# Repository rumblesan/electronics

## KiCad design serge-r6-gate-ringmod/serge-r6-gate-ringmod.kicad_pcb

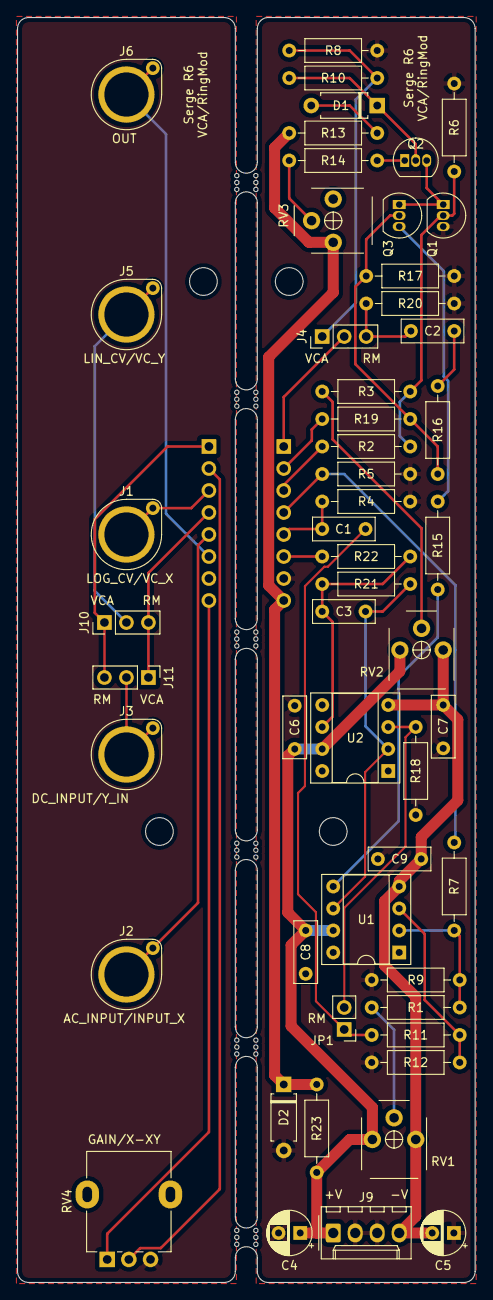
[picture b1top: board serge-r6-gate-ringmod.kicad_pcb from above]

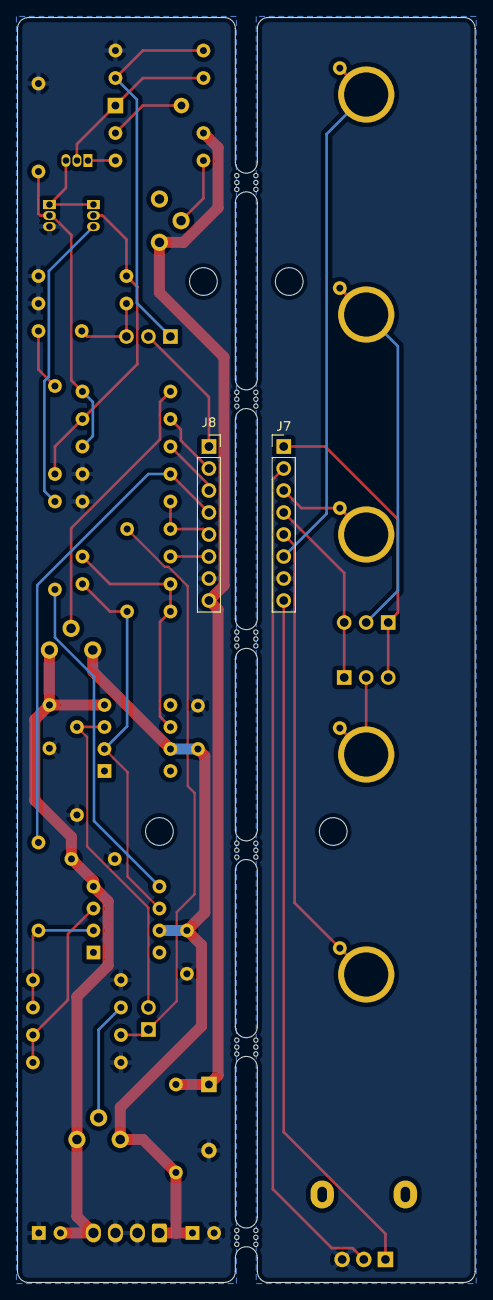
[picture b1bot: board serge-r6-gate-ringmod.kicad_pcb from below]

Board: 2 copper layers, 52.8 x 146.1 mm, 65 parts (2 on the bottom side), 40 nets.

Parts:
C1: 470n; C_Rect_L7.0mm_W2.5mm_P5.00mm
C2: na/470n; C_Rect_L7.0mm_W2.5mm_P5.00mm
C3: 220pf; C_Rect_L7.0mm_W2.5mm_P5.00mm
C4, C5: 10uf; CP_Radial_D5.0mm_P2.50mm
C6, C7, C8, C9: 100nf; C_Rect_L7.0mm_W2.5mm_P5.00mm
D1: 1N4148; Diode_THT_P7.62mm_Horizontal
D2: 6V_Zener; Diode_THT_P7.62mm_Horizontal
H1, H2, H3, H4: MountingScrew_M3_Flathead; MountingHole_3.2mm_M3
J1: LOG_CV/VC_X; BananaJack_THT_JohnsonCinch_108-09
J2: AC_INPUT/INPUT_X; BananaJack_THT_JohnsonCinch_108-09
J3: DC_INPUT/Y_IN; BananaJack_THT_JohnsonCinch_108-09
J4: LIN_CV_INPUT_Y_SEL; PinHeader_1x03_P2.54mm_Vertical
J5: LIN_CV/VC_Y; BananaJack_THT_JohnsonCinch_108-09
J6: OUT; BananaJack_THT_JohnsonCinch_108-09
J7: CTRL_HEADER; PinHeader_1x08_P2.54mm_Vertical
J8: MAIN_HEADER; PinSocket_1x08_P2.54mm_Vertical
J9: Conn_01x04_Male; Molex_KK-254_AE-6410-04A_1x04_P2.54mm_Vertical
J10: LIN_CV_Y_IN_SEL; PinHeader_1x03_P2.54mm_Vertical
J11: DC_IN_VC_Y_SEL; PinHeader_1x03_P2.54mm_Vertical
JP1: Jumper_NO_Small; PinHeader_1x02_P2.54mm_Vertical
Q1, Q2, Q3: 2N3906; TO-92_Inline
R1, R3, R10, R13: 220k; Resistor_THT_L6.3mm_D2.5mm_P10.16mm_Horizontal
R2, R19: 22k/47k; Resistor_THT_L6.3mm_D2.5mm_P10.16mm_Horizontal
R4, R5: 22k; Resistor_THT_L6.3mm_D2.5mm_P10.16mm_Horizontal
R6, R17: 1k; Resistor_THT_L6.3mm_D2.5mm_P10.16mm_Horizontal
R7: 68k/150k; Resistor_THT_L6.3mm_D2.5mm_P10.16mm_Horizontal
R8, R15: 15k; Resistor_THT_L6.3mm_D2.5mm_P10.16mm_Horizontal
R9, R12, R22: 330r; Resistor_THT_L6.3mm_D2.5mm_P10.16mm_Horizontal
R11: 68k; Resistor_THT_L6.3mm_D2.5mm_P10.16mm_Horizontal
R14, R23: 2k2; Resistor_THT_L6.3mm_D2.5mm_P10.16mm_Horizontal
R16, R20: na/47k; Resistor_THT_L6.3mm_D2.5mm_P10.16mm_Horizontal
R18: 33k/na; Resistor_THT_L6.3mm_D2.5mm_P10.16mm_Horizontal
R21: 33k/68k; Resistor_THT_L6.3mm_D2.5mm_P10.16mm_Horizontal
RV1, RV2, RV3: 25k; Potentiometer_THT_Bourns_3306P_Vertical
RV4: 100k; Potentiometer_Alpha_RD901F-40-00D_Single_Vertical
U1: CA3080; DIP-8_W7.62mm_Socket
U2: TL071; DIP-8_W7.62mm_Socket
mouse-bite-2.54mm-slot, mouse-bite-2.54mm-slot#2, mouse-bite-2.54mm-slot#3, mouse-bite-2.54mm-slot#4, mouse-bite-2.54mm-slot#5, mouse-bite-2.54mm-slot#6: VAL**; mouse-bite-2.54mm-slot

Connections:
+6V: D2.1, J8.8, R13.1, R23.1, RV3.1
+12V: C4.1, C6.1, C8.1, J9.1, R23.2, RV1.1, RV2.1, U1.7, U2.7
-12V: C5.2, C7.2, C9.2, J9.4, RV1.3, RV2.3, U1.4, U2.4
/6V_CTRL: J7.8, RV4.1
/AC_IN_X_IN_CTRL: J2.1, J7.5
/AC_IN_X_IN_MAIN: C1.2, J8.5, R4.1
/DC_IN_CTRL: J7.4, J10.3, J11.1
/DC_IN_VC_Y_MAIN: J8.4, R5.1, R7.2
/GAIN_X_XY_CTRL: J7.2, RV4.2
/GAIN_X_XY_MAIN: J8.2, R19.1
/LIN_CV: J4.1, R8.1, R10.2
/LIN_CV_CTRL: J7.1, J10.1, J11.3
/LIN_CV_Y_IN_MAIN: J4.2, J8.1
/LOG_CV_VC_X_CTRL: J1.1, J7.3
/LOG_CV_VC_X_MAIN: J8.3, R2.2
/OUT_CTRL: J6.1, J7.6
/OUT_MAIN: J8.6, R22.1
GND: C4.2, C5.1, C6.2, C7.1, C8.2, C9.1, D2.2, J8.7, J9.2, J9.3, Q1.3, R4.2, R5.2, R6.2, R8.2, R9.2, R12.2, R17.2, R18.2, R20.2
GND1: J7.7, RV4.3
unnamed: C1.1, JP1.1, R11.2
unnamed: C2.1, J4.3, R20.1
unnamed: C2.2, R16.1
unnamed: C3.1, R21.1, R22.2, U2.6
unnamed: C3.2, R21.2, U1.6, U2.2
unnamed: D1.1, Q2.2, R10.1
unnamed: D1.2, R13.2
unnamed: J5.1, J10.2
unnamed: J3.1, J11.2
unnamed: JP1.2, R18.1, U2.3
unnamed: Q1.1, Q2.3, Q3.1
unnamed: Q1.2, R2.1, R3.1, R6.1
unnamed: Q2.1, R14.2
unnamed: Q3.2, R16.2, R17.1, R19.2
unnamed: Q3.3, R15.1
unnamed: R1.1, R7.1, R9.1, U1.2
unnamed: R1.2, RV1.2
unnamed: R3.2, RV2.2
unnamed: R11.1, R12.1, U1.3
unnamed: R14.1, RV3.2
unnamed: R15.2, U1.5

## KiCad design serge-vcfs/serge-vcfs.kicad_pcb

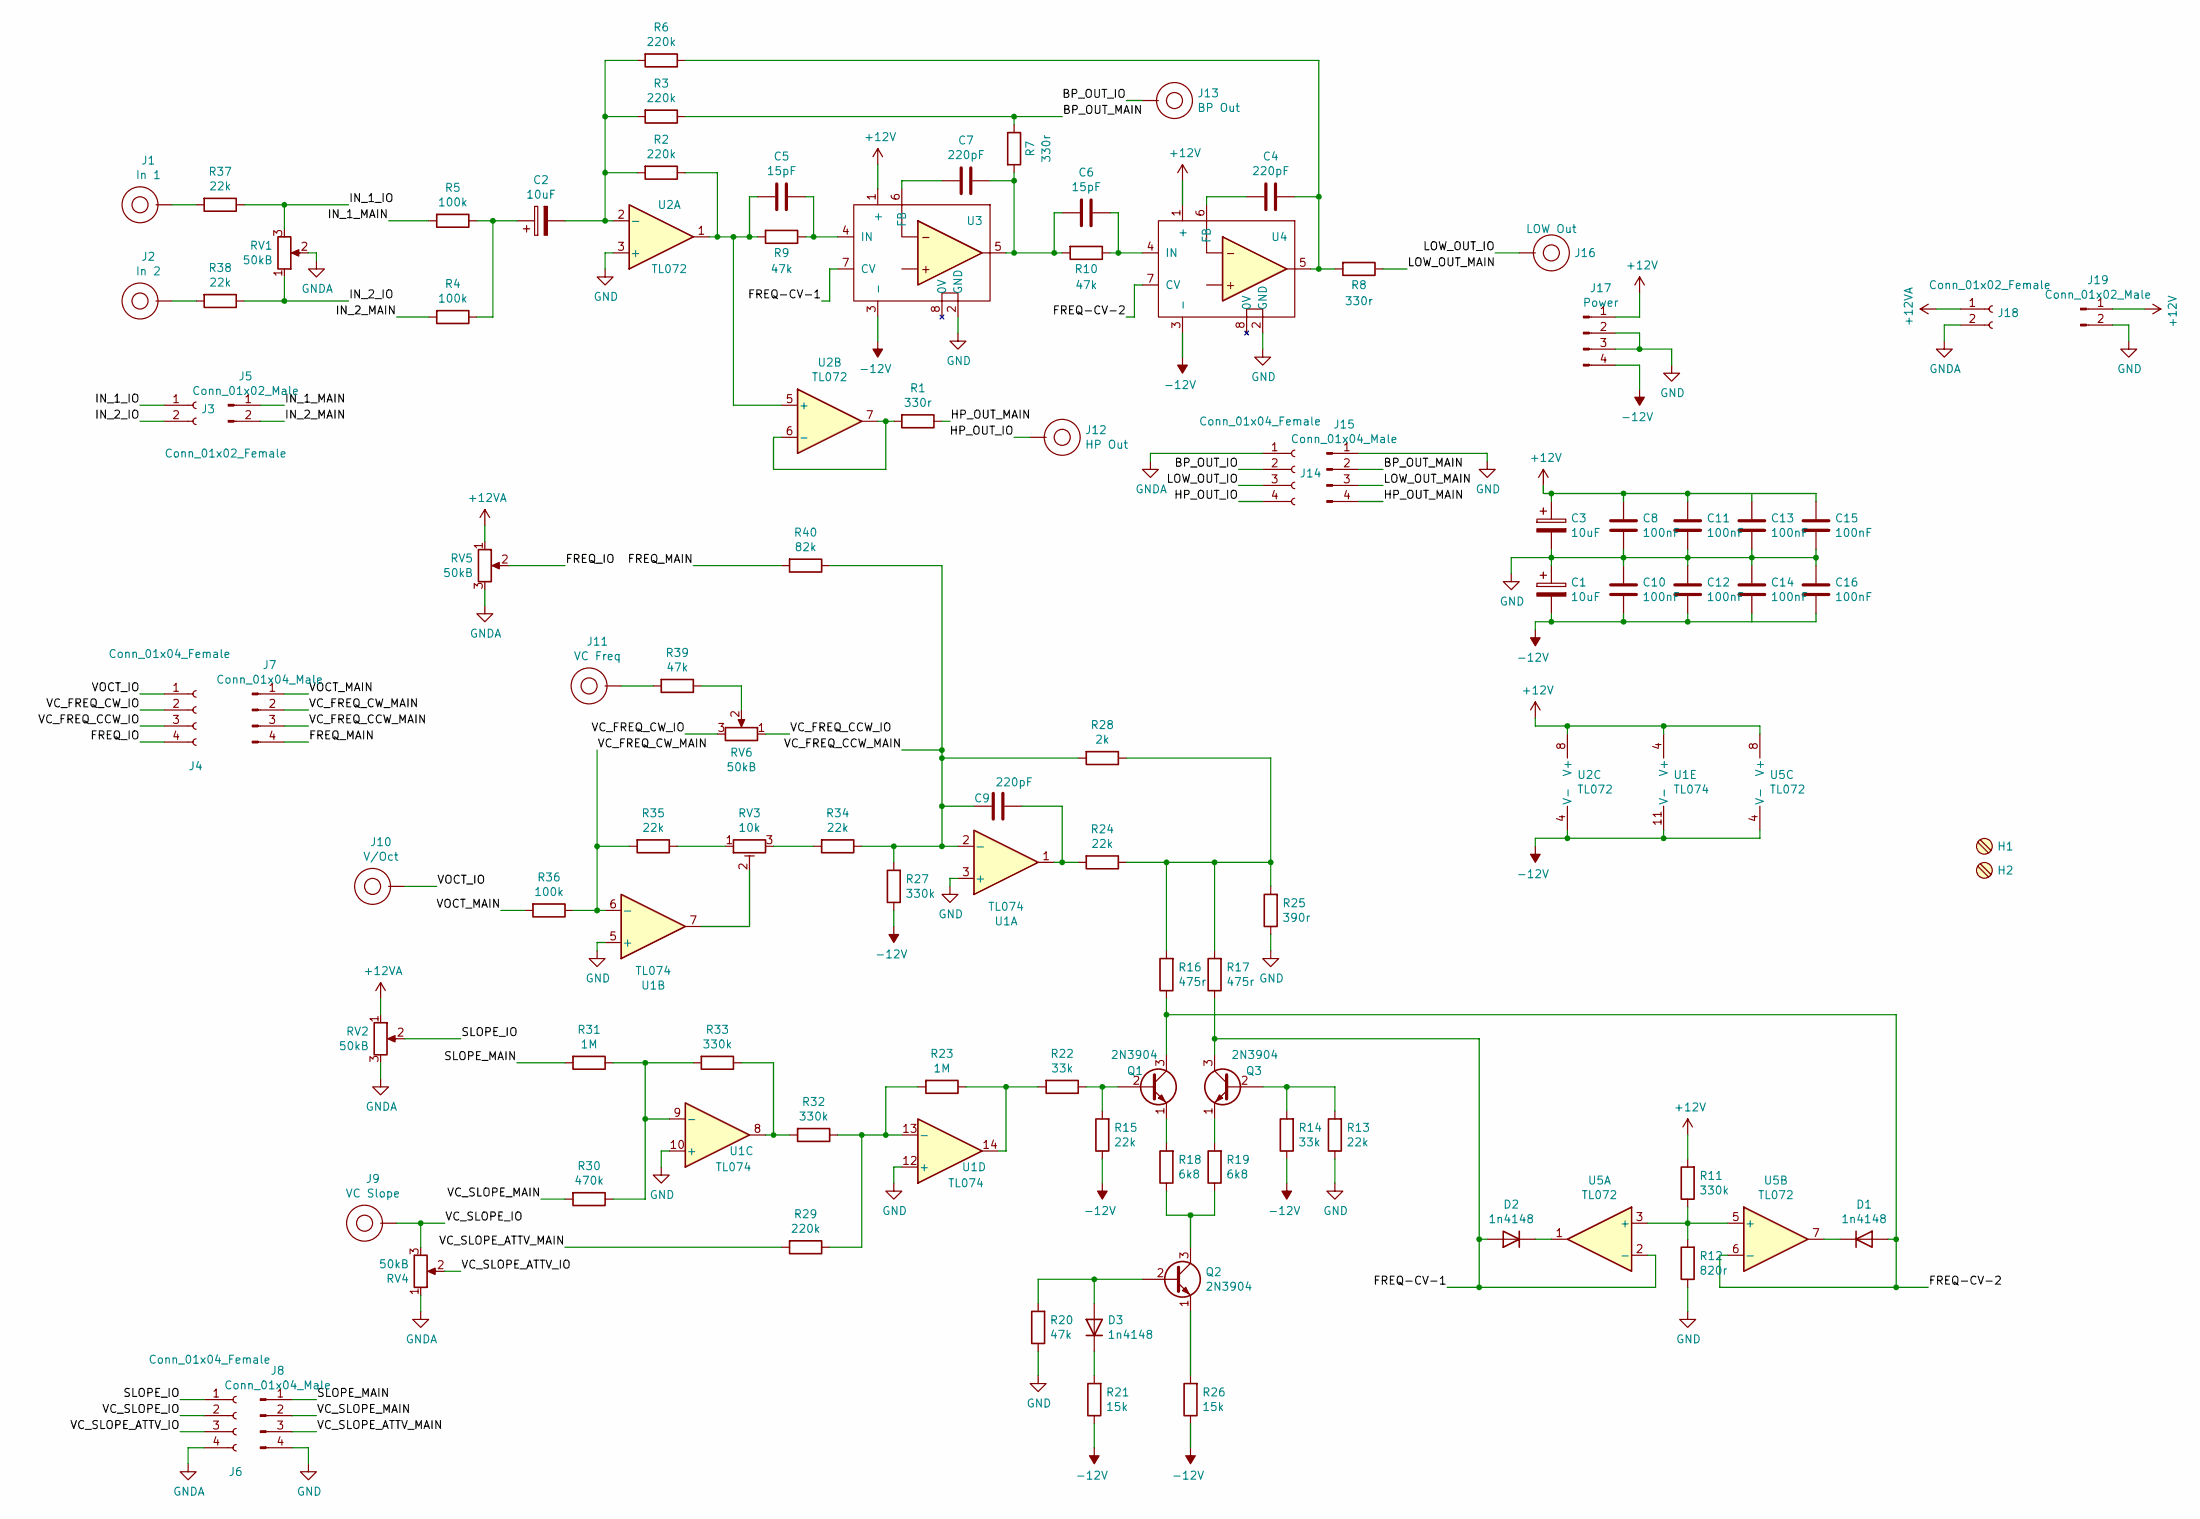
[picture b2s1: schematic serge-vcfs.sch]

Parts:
C1, C2, C3: 10uF; CP_Radial_D5.0mm_P2.50mm
C4, C7: 220pF; C_Axial_L12.0mm_D5.0mm_P15.00mm_Horizontal
C5, C6: 15pF; C_Rect_L7.0mm_W3.5mm_P5.00mm
C8, C10, C11, C12, C13, C14, C15, C16: 100nF; C_Rect_L7.0mm_W3.5mm_P5.00mm
C9: 220pF; C_Rect_L7.0mm_W3.5mm_P5.00mm
D1, D2, D3: 1n4148; Diode_THT_P7.62mm_Horizontal
H1, H2: MountingScrew_M3_Flathead; MountingHole_3.2mm_M3
J1: In 1; BananaJack_THT_JohnsonCinch_108-09
J2: In 2; BananaJack_THT_JohnsonCinch_108-09
J3: Conn_01x02_Female; PinHeader_1x02_P2.54mm_Vertical
J4, J6, J14: Conn_01x04_Female; PinHeader_1x04_P2.54mm_Vertical
J5: Conn_01x02_Male; PinSocket_1x02_P2.54mm_Vertical
J7, J8, J15: Conn_01x04_Male; PinSocket_1x04_P2.54mm_Vertical
J9: VC Slope; BananaJack_THT_JohnsonCinch_108-09
J10: V/Oct; BananaJack_THT_JohnsonCinch_108-09
J11: VC Freq; BananaJack_THT_JohnsonCinch_108-09
J12: HP Out; BananaJack_THT_JohnsonCinch_108-09
J13: BP Out; BananaJack_THT_JohnsonCinch_108-09
J16: LOW Out; BananaJack_THT_JohnsonCinch_108-09
J17: Power; Molex_KK-254_AE-6410-04A_1x04_P2.54mm_Vertical
J18: Conn_01x02_Female; PinSocket_1x02_P2.54mm_Vertical
J19: Conn_01x02_Male; PinHeader_1x02_P2.54mm_Vertical
Q1, Q2, Q3: 2N3904; TO-92_Inline
R1, R7, R8: 330r; R_Axial_DIN0207_L6.3mm_D2.5mm_P7.62mm_Horizontal
R2, R3, R6, R29: 220k; R_Axial_DIN0207_L6.3mm_D2.5mm_P7.62mm_Horizontal
R4, R5, R36: 100k; R_Axial_DIN0207_L6.3mm_D2.5mm_P7.62mm_Horizontal
R9, R10, R20, R39: 47k; R_Axial_DIN0207_L6.3mm_D2.5mm_P7.62mm_Horizontal
R11, R27, R32, R33: 330k; R_Axial_DIN0207_L6.3mm_D2.5mm_P7.62mm_Horizontal
R12: 820r; R_Axial_DIN0207_L6.3mm_D2.5mm_P7.62mm_Horizontal
R13, R15, R24, R34, R35, R37, R38: 22k; R_Axial_DIN0207_L6.3mm_D2.5mm_P7.62mm_Horizontal
R14, R22: 33k; R_Axial_DIN0207_L6.3mm_D2.5mm_P7.62mm_Horizontal
R16, R17: 475r; R_Axial_DIN0207_L6.3mm_D2.5mm_P7.62mm_Horizontal
R18, R19: 6k8; R_Axial_DIN0207_L6.3mm_D2.5mm_P7.62mm_Horizontal
R21, R26: 15k; R_Axial_DIN0207_L6.3mm_D2.5mm_P7.62mm_Horizontal
R23, R31: 1M; R_Axial_DIN0207_L6.3mm_D2.5mm_P7.62mm_Horizontal
R25: 390r; R_Axial_DIN0207_L6.3mm_D2.5mm_P7.62mm_Horizontal
R28: 2k; R_Axial_DIN0207_L6.3mm_D2.5mm_P7.62mm_Horizontal
R30: 470k; R_Axial_DIN0207_L6.3mm_D2.5mm_P7.62mm_Horizontal
R40: 82k; R_Axial_DIN0207_L6.3mm_D2.5mm_P7.62mm_Horizontal
RV1, RV2, RV4, RV5, RV6: 50kB; Potentiometer_Alpha_RD901F-40-00D_Single_Vertical_CircularH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
RV3: 10k; Potentiometer_THT_Bourns_3306P_Vertical
U1: TL074; DIP-14_W7.62mm_Socket
U2, U5: TL072; DIP-8_W7.62mm_Socket
U3, U4: CGS108_Serge_Gain_Cell; Serge_GainCell_Vertical

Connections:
+12V: C3.1, C8.1, C11.1, C13.1, C15.1, J17.1, J19.1, R11.2, U1.4 (V+), U2.8 (V+), U3.1 (+), U4.1 (+), U5.8 (V+)
+12VA: J18.1, RV2.1, RV5.1
-12V: C1.2, C10.2, C12.2, C14.2, C16.2, J17.4, R14.1, R15.1, R21.1, R26.1, R27.1, U1.11 (V-), U2.4 (V-), U3.3 (-), U4.3 (-), U5.4 (V-)
/BP_OUT_IO: J13.1, J14.2
/BP_OUT_MAIN: J15.2, R3.1, R7.1
/FREQ-CV-1: D2.2 (A), Q3.3 (C), R17.1, U3.7 (CV), U5.2 (-)
/FREQ-CV-2: D1.2 (A), Q1.3 (C), R16.1, U4.7 (CV), U5.6 (-)
/FREQ_IO: J4.4, RV5.2
/FREQ_MAIN: J7.4, R40.2
/HP_OUT_IO: J12.1, J14.4
/HP_OUT_MAIN: J15.4, R1.1
/IN_1_IO: J3.1, R37.1, RV1.3
/IN_1_MAIN: J5.1, R5.2
/IN_2_IO: J3.2, R38.1, RV1.1
/IN_2_MAIN: J5.2, R4.2
/LOW_OUT_IO: J14.3, J16.1
/LOW_OUT_MAIN: J15.3, R8.1
/SLOPE_IO: J6.1, RV2.2
/SLOPE_MAIN: J8.1, R31.2
/VC_FREQ_CCW_IO: J4.3, RV6.1
/VC_FREQ_CCW_MAIN: C9.2, J7.3, R27.2, R28.2, R34.1, R40.1, U1.2 (-)
/VC_FREQ_CW_IO: J4.2, RV6.3
/VC_FREQ_CW_MAIN: J7.2, R35.2, R36.1, U1.6 (-)
/VC_SLOPE_ATTV_IO: J6.3, RV4.2
/VC_SLOPE_ATTV_MAIN: J8.3, R29.2
/VC_SLOPE_IO: J6.2, J9.1, RV4.3
/VC_SLOPE_MAIN: J8.2, R30.2
/VOCT_IO: J4.1, J10.1
/VOCT_MAIN: J7.1, R36.2
GND: C1.1, C3.2, C8.2, C10.1, C11.2, C12.1, C13.2, C14.1, C15.2, C16.1, J8.4, J15.1, J17.2, J17.3, J19.2, R12.1, R13.1, R20.1, R25.1, U1.3 (+), U1.5 (+), U1.10 (+), U1.12 (+), U2.3 (+), U3.2 (GND), U4.2 (GND)
GNDA: J6.4, J14.1, J18.2, RV1.2, RV2.3, RV4.1, RV5.3
unnamed: C2.1, R4.1, R5.1
unnamed: C2.2, R2.2, R3.2, R6.2, U2.2 (-)
unnamed: C4.1, R6.1, R8.2, U4.5
unnamed: C4.2, U4.6 (FB)
unnamed: C5.1, R9.1, U3.4 (IN)
unnamed: C5.2, R2.1, R9.2, U2.1, U2.5 (+)
unnamed: C6.1, R10.1, U4.4 (IN)
unnamed: C6.2, C7.1, R7.2, R10.2, U3.5
unnamed: C7.2, U3.6 (FB)
unnamed: C9.1, R24.2, U1.1
unnamed: D1.1 (K), U5.7
unnamed: D2.1 (K), U5.1
unnamed: D3.1 (K), R21.2
unnamed: D3.2 (A), Q2.2 (B), R20.2
unnamed: J1.1, R37.2
unnamed: J2.1, R38.2
unnamed: J11.1, R39.2
unnamed: Q1.1 (E), R18.2
unnamed: Q1.2 (B), R15.2, R22.1
unnamed: Q2.1 (E), R26.2
unnamed: Q2.3 (C), R18.1, R19.1
unnamed: Q3.1 (E), R19.2
unnamed: Q3.2 (B), R13.2, R14.2
unnamed: R1.2, U2.6 (-), U2.7
unnamed: R11.1, R12.2, U5.3 (+), U5.5 (+)
unnamed: R16.2, R17.2, R24.1, R25.2, R28.1
unnamed: R22.2, R23.1, U1.14
unnamed: R23.2, R29.1, R32.1, U1.13 (-)
unnamed: R30.1, R31.1, R33.2, U1.9 (-)
unnamed: R32.2, R33.1, U1.8
unnamed: R34.2, RV3.3
unnamed: R35.1, RV3.1
unnamed: R39.1, RV6.2
unnamed: RV3.2, U1.7

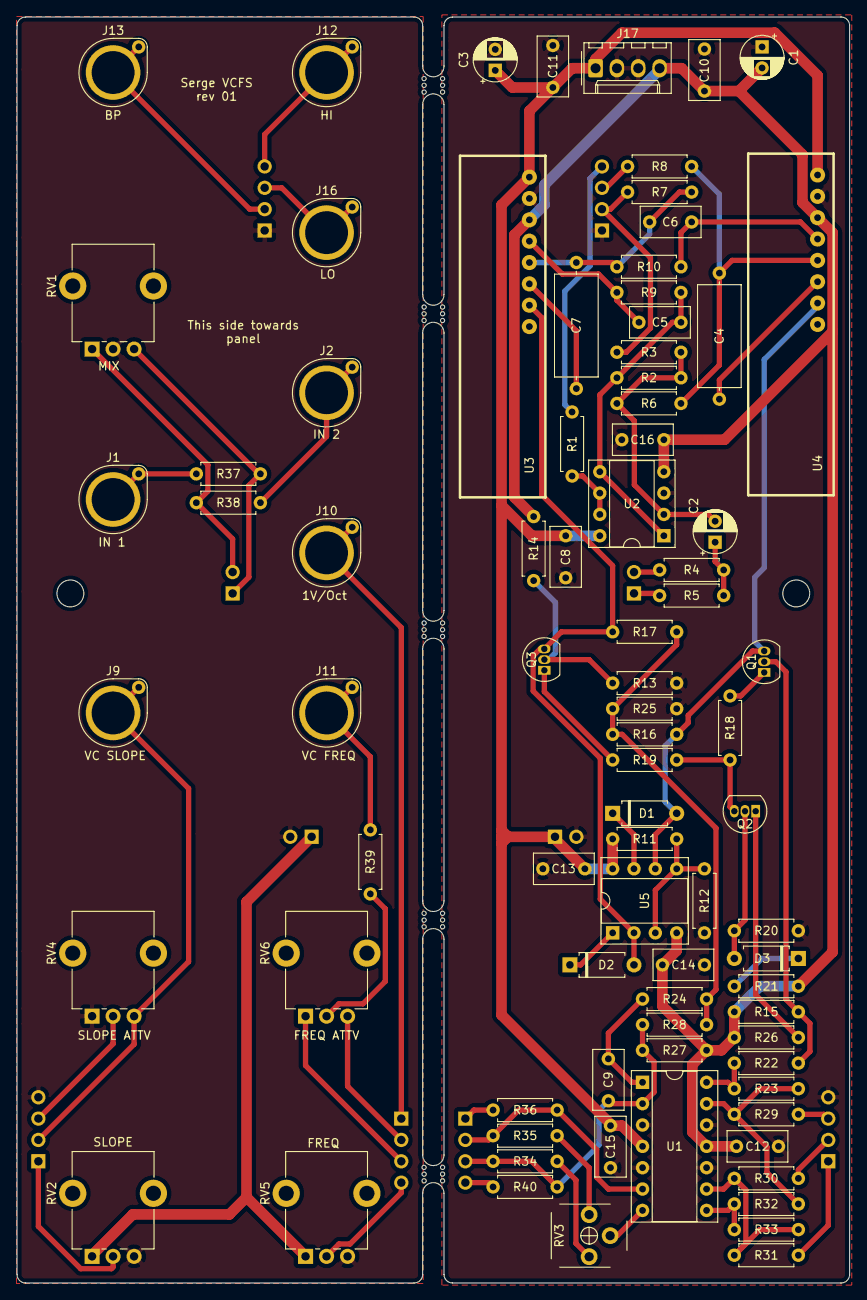
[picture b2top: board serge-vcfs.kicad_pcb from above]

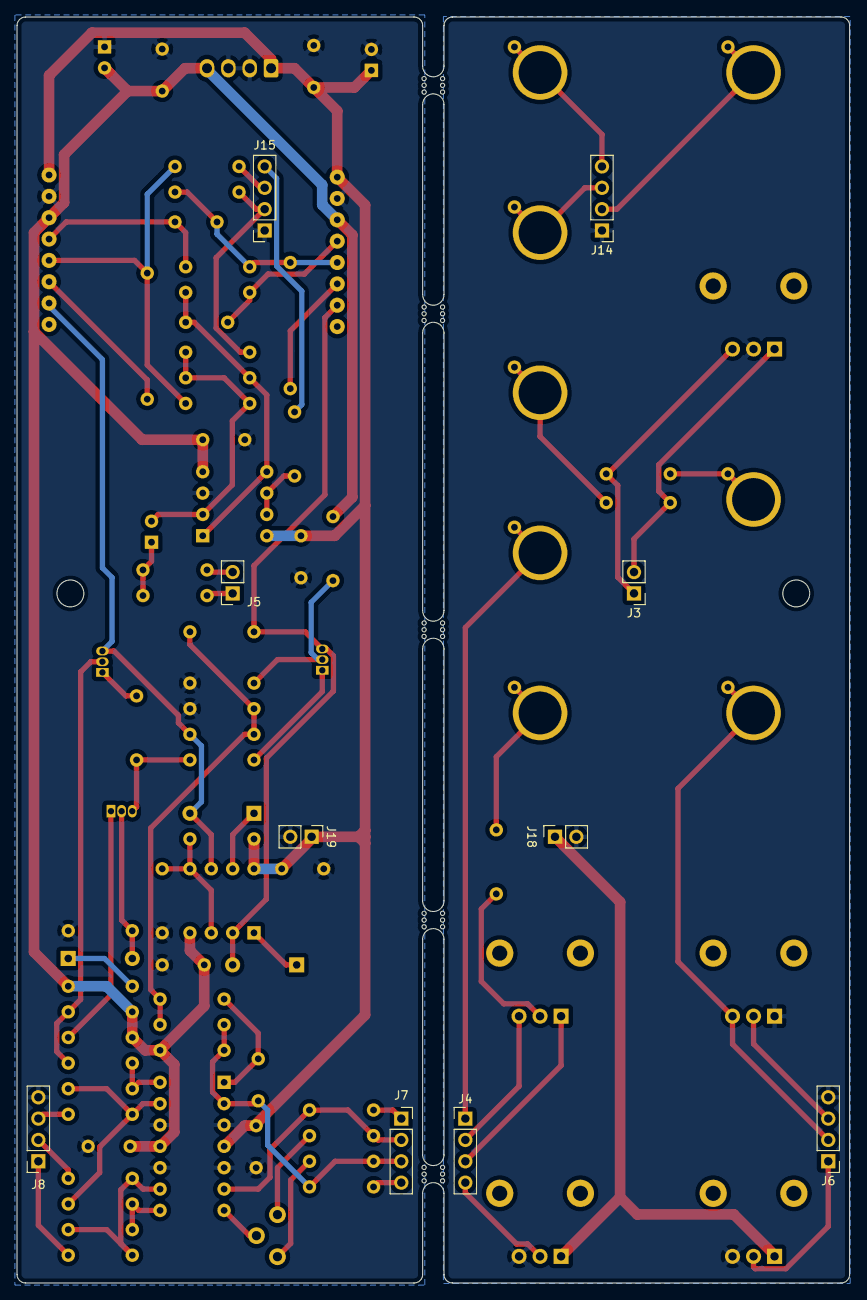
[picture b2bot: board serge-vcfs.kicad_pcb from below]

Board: 2 copper layers, 99.1 x 150.6 mm, 99 parts (10 on the bottom side), 65 nets.

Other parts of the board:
mouse-bite-2.54mm-slot, mouse-bite-2.54mm-slot#2, mouse-bite-2.54mm-slot#3, mouse-bite-2.54mm-slot#4, mouse-bite-2.54mm-slot#5: VAL**; mouse-bite-2.54mm-slot

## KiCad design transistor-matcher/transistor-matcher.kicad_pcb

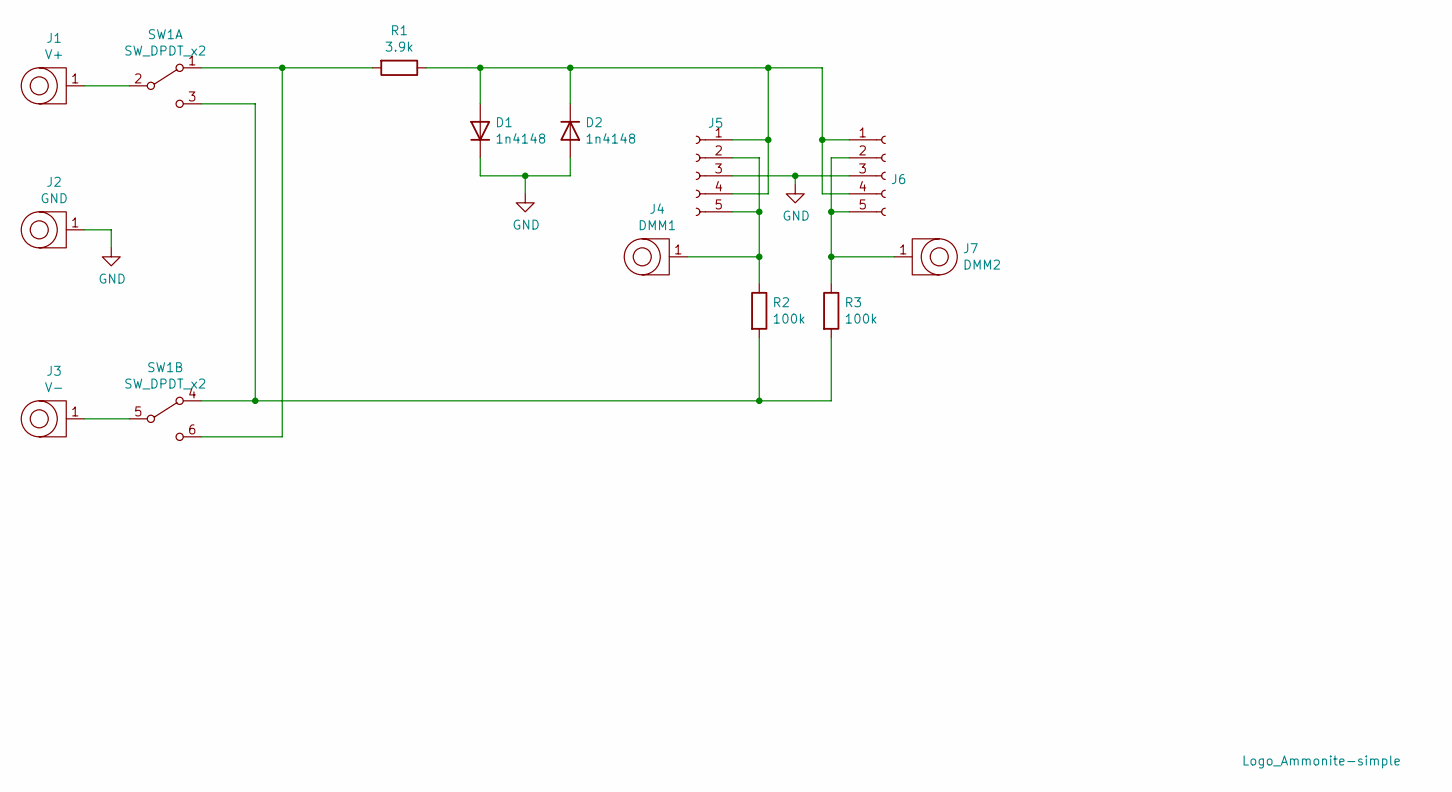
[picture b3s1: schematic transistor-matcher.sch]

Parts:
D1, D2: 1n4148; D_A-405_P7.62mm_Horizontal
H1: Logo_Ammonite-simple; Logo_Ammonite-simple_10.4mmx12.0mm
J1: V+; Deltron_571_PCB_BananaJack
J2: GND; Deltron_571_PCB_BananaJack
J3: V-; Deltron_571_PCB_BananaJack
J4: DMM1; Deltron_571_PCB_BananaJack
J5, J6: Conn_01x05_Female; TransistorTestSocket_1x05_P2.54mm_Vertical
J7: DMM2; Deltron_571_PCB_BananaJack
R1: 3.9k; R_Axial_DIN0309_L9.0mm_D3.2mm_P12.70mm_Horizontal
R2, R3: 100k; R_Axial_DIN0309_L9.0mm_D3.2mm_P12.70mm_Horizontal
SW1: SW_DPDT_x2; SW_E-Switch-EG2201_DPDT

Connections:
GND: D1.1 (K), D2.2 (A), J2.1, J5.3, J6.3
unnamed: D1.2 (A), D2.1 (K), J5.1, J5.4, J6.1, J6.4, R1.1
unnamed: J1.1, SW1.2 (B)
unnamed: J3.1, SW1.5 (B)
unnamed: J4.1, J5.2, J5.5, R2.1
unnamed: J6.2, J6.5, J7.1, R3.1
unnamed: R1.2, SW1.1 (A), SW1.6 (C)
unnamed: R2.2, R3.2, SW1.3 (C), SW1.4 (A)

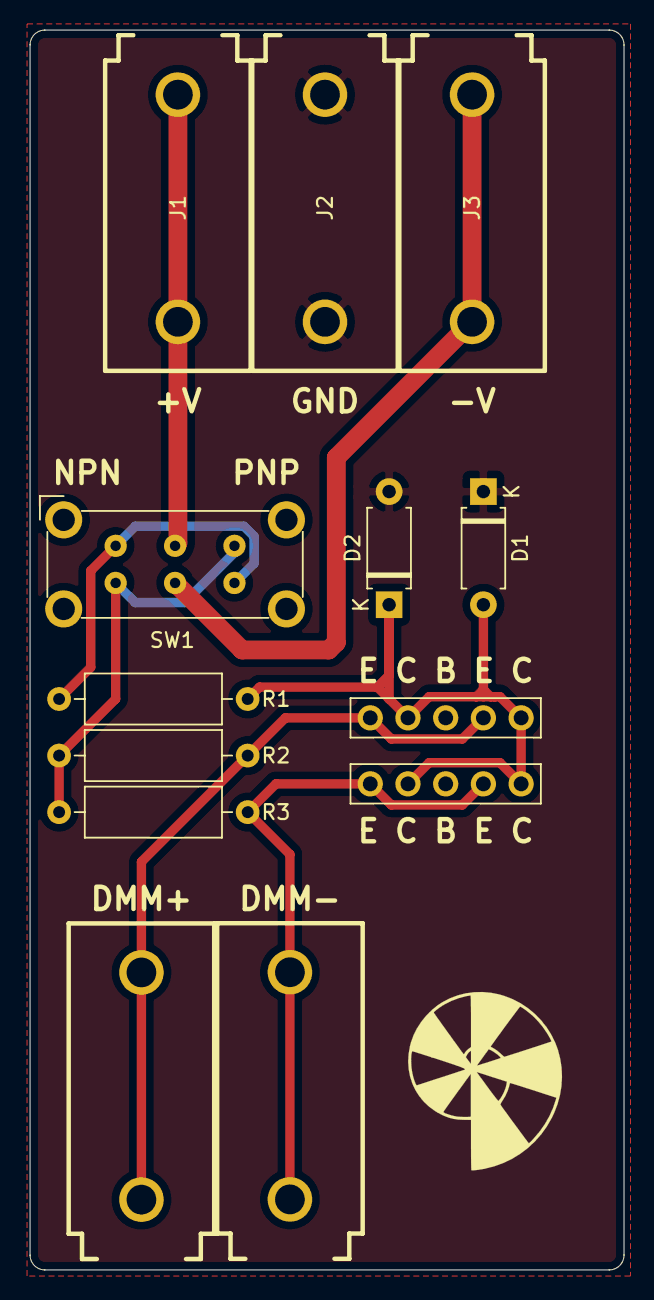
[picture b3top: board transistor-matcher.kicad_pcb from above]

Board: 2 copper layers, 40.0 x 83.5 mm, 14 parts (0 on the bottom side), 8 nets.

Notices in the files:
serge-vcfs/serge-vcfs.sch:
creativecommons.org/licenses/by/4.0
License: CC BY 4.0
